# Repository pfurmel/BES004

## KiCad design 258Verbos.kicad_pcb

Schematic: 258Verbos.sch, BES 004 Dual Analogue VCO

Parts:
0.5W1: 2R2; RESISTOR_R0805
10R1: 0.5W; RESISTOR_R0805
C1, C2: 100uF; CP_Radial_D10.0mm_P2.50mm_P5.00mm
C3, C7: .0047uF; CAPACITOR-WIMA_C5B4.5
C4, C8: 15uF; RESISTOR_E2_5-6E
C5, C9: 100pF; C_Rect_L10_W2.5_P5-7.5
C6, C10: 220pf; C_Rect_L10_W2.5_P5-7.5
CONTROL1: ALPHA-9MMA; TOMW_EVUF
D1, D2, D3, D4: 1N4148DO35-7; DIODE_DO35-7
IC1, IC2: CA3140N; SOIC-8-N
J1, J2: J201; SOT-23_Handsoldering
OSC1_CONTROL1, OSC1_FINE1, OSC1_FM_POT1, OSC1_FREQUENCY1, OSC2_FM_POT1: ALPHA-9MMA; TOMW_EVUF
OSC1_FM_IN1, OSC2_FM_IN1: PJ-301B; TOMW_PJ-301B
OSC1_FREQ_TRIM1: 100K; RCL_RTRIM64W
OSC1_SINE_TRIM1, OSC2_SINE_TRIM1: 20k; RCL_RTRIM64W
OSC1_V/OCT_TRIM1: 100R; RCL_RTRIM64W
OSC_1_CONTROL_IN1, OSC_1_V/OCT1, OSC_2CONTROL_IN1, OSC_2_V/OCT1: PJ-301B; TOMW_PJ-301B
OSC_2_FINE1: ALPHA-9MMA; TOMW_EVUF
OSC_2_FREQ_TRIM1: 100K; RCL_RTRIM64W
OSC_2_V/OCT_TRIM1: 100R; RCL_RTRIM64W
OS_2_FREQUENCY1: ALPHA-9MMA; TOMW_EVUF
Q1, Q4: 2N3906; SOT-23_Handsoldering
Q2, Q5: BC847BS; TRANSISTOR-SMALL-SIGNAL_SOT363_PHILIPS
Q3, Q6: J113; SOT-23_Handsoldering
R1, R44: 390K; RESISTOR_R0805
R2, R45: 3K3; RESISTOR_R0805
R3, R7, R20, R24, R46, R50, R63, R67: 10K; RESISTOR_R0805
R4, R47: 3k3; RESISTOR_R0805
R5, R11, R48, R54: 6k8; RESISTOR_R0805
R6, R49: 6K81; RESISTOR_R0805
R8, R51: 33K; RESISTOR_R0805
R9, R52: 68K; RESISTOR_R0805
R10, R53: 1M5; RESISTOR_R0805
R12, R55: 2K49; RESISTOR_R0805
R13, R56: 4K99; RESISTOR_R0805
R14, R18, R19, R57, R61, R62: 15K; RESISTOR_R0805
R15, R58: 20K; RESISTOR_R0805
R16, R27, R59, R70: 330K; RESISTOR_R0805
R17, R22, R26, R32, R60, R65, R69, R75: 680R; RESISTOR_R0805
R21, R25, R30, R35, R64, R68, R73, R78: 100K; RESISTOR_R0805
R23, R66: 330R; RESISTOR_R0805
R28, R71: 15k; RESISTOR_R0805
R29, R72: 68k; RESISTOR_R0805
R31, R74: 1K8; RESISTOR_R0805
R33, R76: 10k; RESISTOR_R0805
R34, R77: 390R; RESISTOR_R0805
R36, R79: 4M7; RESISTOR_R0805
R37, R80: 100k; RESISTOR_R0805
R38, R81: 180K; RESISTOR_R0805
R39, R41, R82, R84: 680k; RESISTOR_R0805
R40, R83: 150k; RESISTOR_R0805
R42, R85: 820k; RESISTOR_R0805
R43, R86: 330k; RESISTOR_R0805
SAW1: 470R; RESISTOR_R0805
SAW2: 150K; RESISTOR_R0805
SAW3: 820K; RESISTOR_R0805
SAW_OUT1: PJ-301B; TOMW_PJ-301B
SAW_WAVESHAPE1: PJ-301B; TOMW_PJ-301B
SAW_WAVESHAPE_Pot1: ALPHA-9MMA; TOMW_EVUF
SAW_WAVESHAPE_TRIM1: 1M; RCL_RTRIM64W
SQ1: 2K2; RESISTOR_R0805
SQ2: 330K; RESISTOR_R0805
SQ3: 680K; RESISTOR_R0805
SQ_OUT1: PJ-301B; TOMW_PJ-301B
SQ_WAVESHAPE1: PJ-301B; TOMW_PJ-301B
SQ_WAVESHAPE_Pot1: ALPHA-9MMA; TOMW_EVUF
SQ_WAVESHAPE_TRIM1: 1M; RCL_RTRIM64W
SV1: TOMW_MA05-2
T1, T2: BC857BS; NXP_60_SOT363
TEMPCO1, TEMPCO2: 2K; RESISTOR_R0805
U1, U4: TL072; SOIC-8-N
U2: LM13700; SO-16-N
U3, U5: TL074; SOIC-14_N

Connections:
+15V: 0.5W1.1, IC1.7 (V+), IC2.7 (V+), OSC1_FINE1.1 (A), OSC1_FREQUENCY1.1 (A), OSC1_FREQ_TRIM1.3 (E), OSC_2_FINE1.1 (A), OSC_2_FREQ_TRIM1.3 (E), OS_2_FREQUENCY1.1 (A), Q1.3 (E), Q2.3 (C), Q4.3 (E), Q5.3 (C), R2.1, R8.1, R45.1, R51.1, SAW_WAVESHAPE_Pot1.1 (A), SQ_WAVESHAPE_Pot1.1 (A), U1.8 (V+), U2.11 (V+), U3.4 (V+), U4.8 (V+), U5.4 (V+)
-15V: 10R1.1, IC1.4 (V-), IC2.4 (V-), OSC1_FREQ_TRIM1.1 (A), OSC_2_FREQ_TRIM1.1 (A), R10.2, R18.2, R19.2, R43.2, R53.2, R61.2, R62.2, R86.2, U1.4 (V-), U2.6 (V-), U3.11 (V-), U4.4 (V-), U5.11 (V-)
/N$1: Q2.1 (E), Q2.4 (E), R19.1, SAW2.2
/N$2: Q1.2 (B), Q2.6 (C), R2.2
/N$3: Q1.1 (C), R6.1, R9.1
/N$4: Q2.2 (B), R6.2, R12.1, R18.1
/N$5: J1.1 (D), R17.1
/N$6: C3.1, U1.2 (-), U2.12 (OUTPUT)
/N$10: R3.2, T1.1 (E), T1.4 (E)
/N$11: C5.2, IC1.6 (OUT), R3.1
/N$12: C5.1, IC1.2 (-IN), R7.2, R10.1, T1.6 (C)
/N$13: IC1.3 (+IN), R1.1
/N$14: C4.+, R7.1
/N$15: OSC1_V/OCT_TRIM1.2 (S), T1.5 (B)
/N$16: OSC1_V/OCT_TRIM1.1 (A), R34.1
/N$17: OSC1_V/OCT_TRIM1.3 (E), TEMPCO1.2, U3.8
/N$18: OSC1_CONTROL1.3 (E), R21.1, R30.2, R35.2, R36.1, R37.2, TEMPCO1.1, U3.9 (-)
/N$19: R21.2, R25.2, U3.1
/N$20: OSC1_CONTROL1.1 (A), R25.1, U3.2 (-)
/N$21: R20.2, U3.3 (+)
/N$22: R31.2, U3.10 (+)
/N$23: C4.-, OSC1_FM_POT1.2 (S)
/N$24: OSC1_FREQUENCY1.2 (S), R30.1
/N$25: T1.3 (C), U2.16 (AMP_BIAS_INPUT)
/N$33: Q3.1 (D), R29.1, SAW3.2, U3.14
/N$34: C6.2, R22.2, R28.1, U3.7
/N$35: Q3.2 (S), R32.1
/N$36: R32.2, SAW1.1, U3.5 (+)
/N$37: Q3.3 (G), SAW_WAVESHAPE_TRIM1.2 (S)
/N$38: R39.2, R41.2, R42.2, R43.1, SAW_WAVESHAPE_TRIM1.1 (A)
/N$39: R39.1, R40.1, SAW_WAVESHAPE1.P$4 (4)
/N$41: R41.1, SAW_WAVESHAPE_Pot1.2 (S)
/N$43: C6.1, OSC1_SINE_TRIM1.1 (A), R4.1, R28.2, U3.6 (-)
/N$44: OSC1_SINE_TRIM1.2 (S), OSC1_SINE_TRIM1.3 (E), R5.1, R11.2
/N$46: D1.A, D2.A, J1.3 (G), R16.1, R27.1
/N$47: C3.2, D1.C, Q2.5 (B), R11.1, R16.2, R17.2, U1.1
/N$49: J1.2 (S), R26.1, SAW1.2
/N$51: 0.5W1.2, C1.+, SV1.9, SV1.10
/N$52: 10R1.2, C2.-, SV1.1, SV1.2
/OSC2: CONTROL1.1 (A), R68.1, U5.2 (-)
GND: C1.-, C2.+, D2.C, D4.C, OSC1_FINE1.3 (E), OSC1_FM_IN1.P$1 (5), OSC1_FM_IN1.P$2 (5), OSC1_FM_POT1.3 (E), OSC1_FREQUENCY1.3 (E), OSC2_FM_IN1.P$1 (5), OSC2_FM_IN1.P$2 (5), OSC2_FM_POT1.3 (E), OSC_1_CONTROL_IN1.P$1 (5), OSC_1_CONTROL_IN1.P$2 (5), OSC_1_V/OCT1.P$1 (5), OSC_1_V/OCT1.P$2 (5), OSC_2CONTROL_IN1.P$1 (5), OSC_2CONTROL_IN1.P$2 (5), OSC_2_FINE1.3 (E), OSC_2_V/OCT1.P$1 (5), OSC_2_V/OCT1.P$2 (5), OS_2_FREQUENCY1.3 (E), R1.2, R4.2, R5.2, R12.2, R13.2, R14.2, R20.1, R24.2, R26.2, R27.2, R31.1, R33.1, R34.2, R40.2, R42.1, R44.2, R47.2, R48.2, R55.2, R56.2, R57.2, R63.1, R67.2, R69.2, R70.2, R74.1, R76.1, R77.2, R83.2, R85.1, SAW_OUT1.P$1 (5), SAW_OUT1.P$2 (5), SAW_WAVESHAPE1.P$1 (5), SAW_WAVESHAPE1.P$2 (5), SAW_WAVESHAPE_Pot1.3 (E), SQ3.1, SQ_OUT1.P$1 (5), SQ_OUT1.P$2 (5), SQ_WAVESHAPE1.P$1 (5), SQ_WAVESHAPE1.P$2 (5), SQ_WAVESHAPE_Pot1.3 (E), SV1.3, SV1.4, SV1.5, SV1.6, SV1.7, SV1.8, T1.2 (B), T2.2 (B), U1.3 (+), U4.3 (+)
unnamed: C7.1, U2.5 (OUTPUT), U4.2 (-)
unnamed: C7.2, D3.C, Q5.5 (B), R54.1, R59.2, R60.2, U4.1
unnamed: C8.+, R50.1
unnamed: C8.-, OSC2_FM_POT1.2 (S)
unnamed: C9.1, IC2.2 (-IN), R50.2, R53.1, T2.6 (C)
unnamed: C9.2, IC2.6 (OUT), R46.1
unnamed: C10.1, OSC2_SINE_TRIM1.1 (A), R47.1, R71.2, U5.13 (-)
unnamed: C10.2, R65.2, R71.1, U5.14
unnamed: CONTROL1.2 (S), R81.2
unnamed: CONTROL1.3 (E), R64.1, R73.2, R78.2, R79.1, R80.2, TEMPCO2.1, U5.6 (-)
unnamed: D3.A, D4.A, J2.3 (G), R59.1, R70.1
unnamed: IC2.3 (+IN), R44.1
unnamed: J2.1 (D), R60.1
unnamed: J2.2 (S), R69.1, SQ1.2
unnamed: OSC1_CONTROL1.2 (S), R38.2
unnamed: OSC1_FINE1.2 (S), R36.2
unnamed: OSC1_FM_IN1.P$4 (4), OSC1_FM_POT1.1 (A)
unnamed: OSC1_FREQ_TRIM1.2 (S), R35.1
unnamed: OSC2_FM_IN1.P$4 (4), OSC2_FM_POT1.1 (A)
unnamed: OSC2_SINE_TRIM1.2 (S), OSC2_SINE_TRIM1.3 (E), R48.1, R54.2
unnamed: OSC_1_CONTROL_IN1.P$4 (4), R38.1
unnamed: OSC_1_V/OCT1.P$4 (4), R37.1
unnamed: OSC_2CONTROL_IN1.P$4 (4), R81.1
unnamed: OSC_2_FINE1.2 (S), R79.2
unnamed: OSC_2_FREQ_TRIM1.2 (S), R78.1
unnamed: OSC_2_V/OCT1.P$4 (4), R80.1
unnamed: OSC_2_V/OCT_TRIM1.1 (A), R77.1
unnamed: OSC_2_V/OCT_TRIM1.2 (S), T2.5 (B)
unnamed: OSC_2_V/OCT_TRIM1.3 (E), TEMPCO2.2, U5.7
unnamed: OS_2_FREQUENCY1.2 (S), R73.1
unnamed: Q4.1 (C), R49.1, R52.1
unnamed: Q4.2 (B), Q5.6 (C), R45.2
unnamed: Q5.1 (E), Q5.4 (E), R62.1
unnamed: Q5.2 (B), R49.2, R55.1, R61.1, SQ2.2
unnamed: Q6.1 (D), R72.1, U5.8
unnamed: Q6.2 (S), R75.1
unnamed: Q6.3 (G), SQ_WAVESHAPE_TRIM1.2 (S)
unnamed: R8.2, R13.1, U2.14 (INPUT(+))
unnamed: R9.2, R14.1, U2.13 (INPUT(-))
unnamed: R15.1, R23.2, U1.7
unnamed: R15.2, R24.1, U1.6 (-)
unnamed: R22.1, U1.5 (+)
unnamed: R23.1, SAW_OUT1.P$4 (4)
unnamed: R29.2, SAW2.1, U3.13 (-)
unnamed: R33.2, U3.12 (+)
unnamed: R46.2, T2.1 (E), T2.4 (E)
unnamed: R51.2, R56.1, U2.3 (INPUT(+))
unnamed: R52.2, R57.1, U2.4 (INPUT(-))
unnamed: R58.1, R66.2, U4.7
unnamed: R58.2, R67.1, U4.6 (-)
unnamed: R63.2, U5.3 (+)
unnamed: R64.2, R68.2, U5.1
unnamed: R65.1, U4.5 (+)
unnamed: R66.1, SQ_OUT1.P$4 (4)
unnamed: R72.2, SQ2.1, U5.9 (-)
unnamed: R74.2, U5.5 (+)
unnamed: R75.2, SQ1.1, U5.12 (+)
unnamed: R76.2, U5.10 (+)
unnamed: R82.1, R83.1, SQ_WAVESHAPE1.P$4 (4)
unnamed: R82.2, R84.2, R85.2, R86.1, SQ_WAVESHAPE_TRIM1.1 (A)
unnamed: R84.1, SQ_WAVESHAPE_Pot1.2 (S)
unnamed: SAW3.1, SAW_WAVESHAPE_TRIM1.3 (E)
unnamed: SQ3.2, SQ_WAVESHAPE_TRIM1.3 (E)
unnamed: T2.3 (C), U2.1 (AMP_BIAS_INPUT)

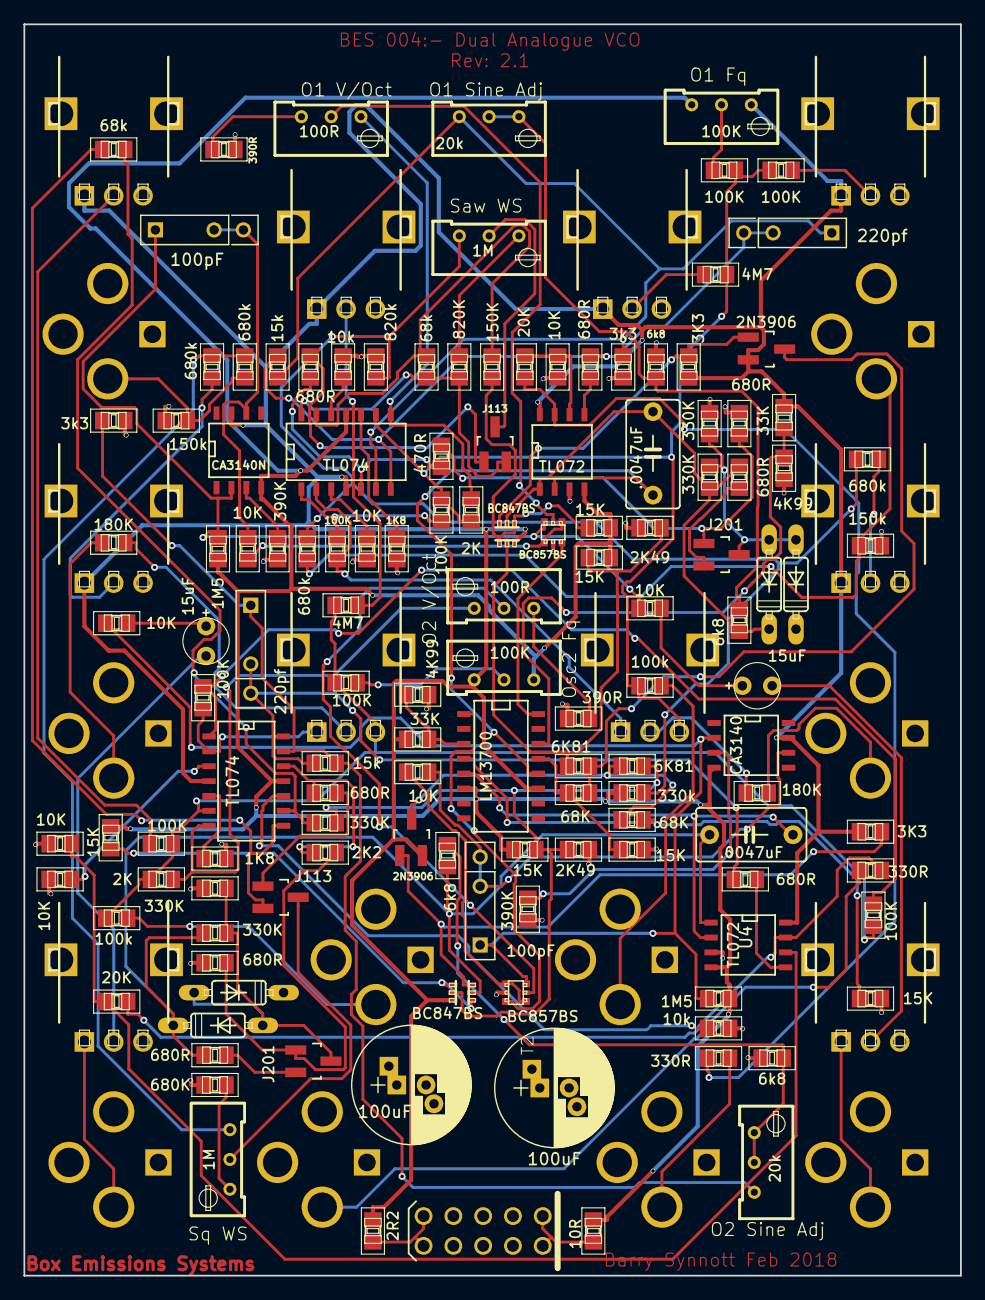
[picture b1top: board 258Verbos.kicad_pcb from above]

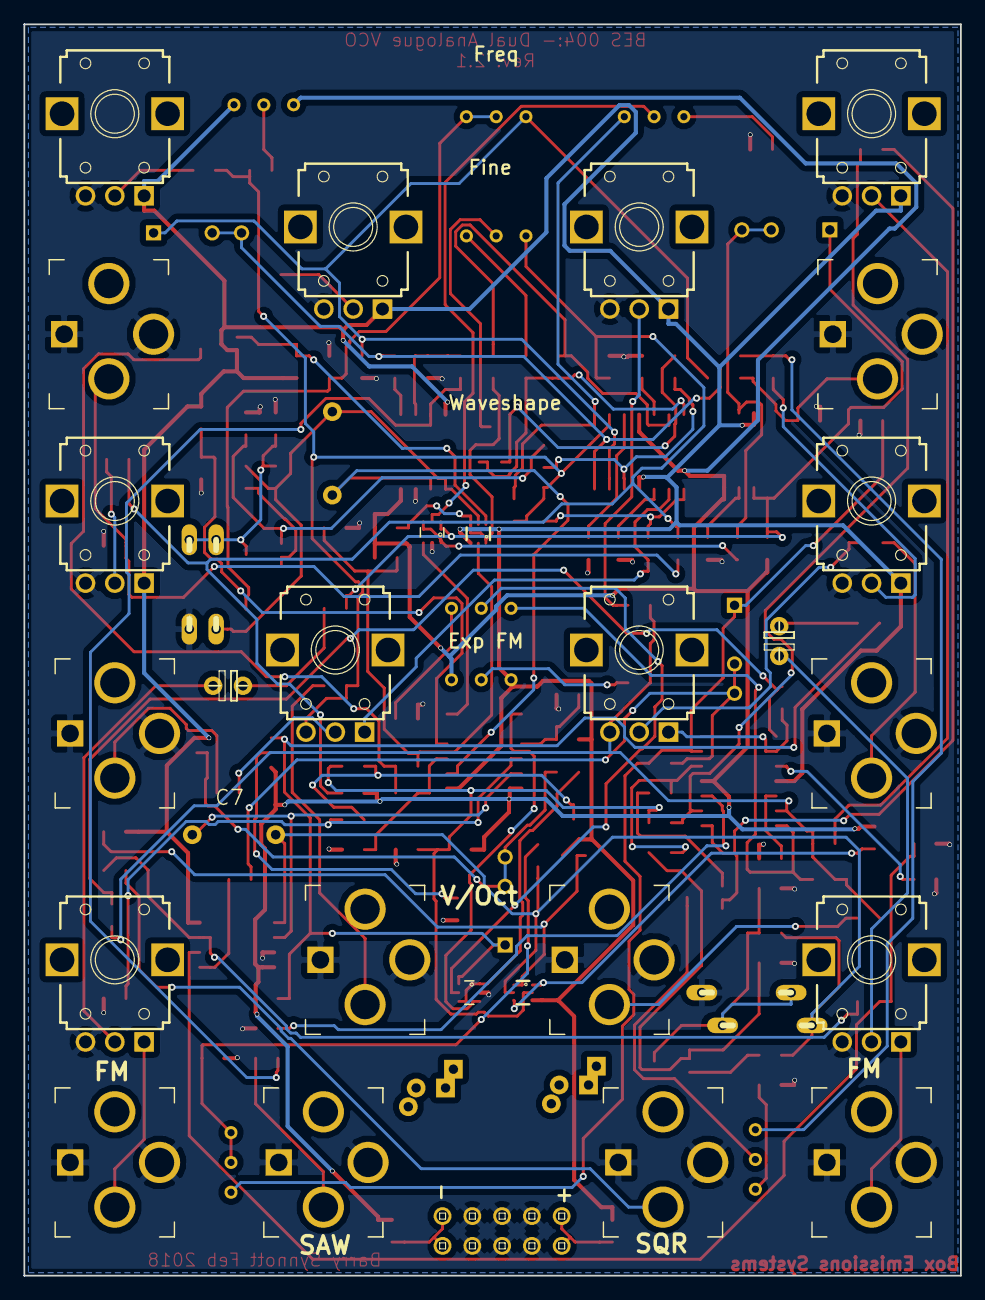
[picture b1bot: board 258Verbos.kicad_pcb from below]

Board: 2 copper layers, 79.9 x 106.7 mm, 154 parts (17 on the bottom side), 105 nets.

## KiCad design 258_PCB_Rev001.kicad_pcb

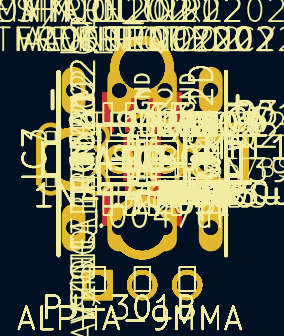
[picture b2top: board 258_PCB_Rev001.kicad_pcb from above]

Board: 2 copper layers, 82 parts (0 on the bottom side), 52 nets, no tracks yet.

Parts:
0.5W202: 33K; RESISTOR_R0805
10R202: 0.5W; RESISTOR_R0805
C2: .0047uF; CAPACITOR-WIMA_C5B4.5
C3: 100pF; CAPACITOR-WIMA_C2.5-3
C4: 15uF; RESISTOR_E2_5-6E
C5: 220pf; CAPACITOR-WIMA_C2.5-3
C6, C7: 100uF; RESISTOR_E2_5-6E
CONTROL202: ALPHA-9MMA; TOMW_EVUF
CONTROL_IN202: PJ-301B; TOMW_PJ-301B
D1, D2: 1N4148DO35-7; DIODE_DO35-7
FINE202: ALPHA-9MMA; TOMW_EVUF
FM_IN202: PJ-301B; TOMW_PJ-301B
FM_POT202: ALPHA-9MMA; TOMW_EVUF
FREQUENCY202: ALPHA-9MMA; TOMW_EVUF
FREQ_TRIM202: 100K; RCL_RTRIM64W
IC2: TL071D; LINEAR_SO08
IC3: CA3140N; LINEAR_DIL08
IC4, IC5B1, IC6A1: TL072D; LINEAR_SO08
IC7: CA3080E; OTA_DIL08
INITIAL_FREQUENCY202: ALPHA-9MMA; TOMW_EVUF
J201: MPF102; BT_TRANSISTOR_TO92F
MAIN_OUT202: PJ-301B; TOMW_PJ-301B
Q1: BC847BS; TRANSISTOR-SMALL-SIGNAL_SOT363_PHILIPS
Q2: 2N3906; TRANSISTOR-PNP_TO92
Q3: MPF102; BT_TRANSISTOR_TO92F
R1, R3, R9: 15K; RESISTOR_R0805
R2: 6K81; RESISTOR_R0805
R4: 2K49; RESISTOR_R0805
R5: 4K99; RESISTOR_R0805
R6: 3K3; RESISTOR_R0805
R7: 33K; RESISTOR_R0805
R8: 68K; RESISTOR_R0805
R10, R12, R19: 10K; RESISTOR_R0805
R11: 390K; RESISTOR_R0805
R13: 1M5; RESISTOR_R0805
R14: 10k; RESISTOR_R0805
R15: 390R; RESISTOR_R0805
R16, R17, R18, R21: 100K; RESISTOR_R0805
R20: 1K8; RESISTOR_R0805
R22: 180K; RESISTOR_R0805
R23: 100k; RESISTOR_R0805
R24: 68k; RESISTOR_R0805
R25, R31, R36, R37: 680R; RESISTOR_R0805
R26: 330k; RESISTOR_R0805
R27, R29: 680k; RESISTOR_R0805
R28: 150k; RESISTOR_R0805
R30: 820k; RESISTOR_R0805
R32: 15k; RESISTOR_R0805
R33, R34: 6k8; RESISTOR_R0805
R35: 3k3; RESISTOR_R0805
R38, R39: 330K; RESISTOR_R0805
SIN/SQ1, SIN/SQ2, SIN/SQ3, SIN/SQ4, SIN/SQ5: 0; RESISTOR_R0805
SINE_TRIM202: 20k; RCL_RTRIM64W
SV1: TOMW_MA05-2
T1: BC857BS; NXP_60_SOT363
TEMPCO202: 2K; RESISTOR_R0805
V/OCT202: PJ-301B; TOMW_PJ-301B
V/OCT_TRIM202: 100R; RCL_RTRIM64W
WAVESHAPE202: ALPHA-9MMA; TOMW_EVUF
WAVESHAPE_CTRL202: PJ-301B; TOMW_PJ-301B
WAVESHAPE_TRIM202: 1M; RCL_RTRIM64W

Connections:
+15V: 0.5W202.1, FREQUENCY202.3, FREQ_TRIM202.3, IC2.7, IC3.7, INITIAL_FREQUENCY202.3, Q1.3, Q2.3, R6.1, R7.2, SV1.9, WAVESHAPE202.3
-15V: 10R202.1, FREQ_TRIM202.1, IC2.4, IC3.4, INITIAL_FREQUENCY202.1, R1.2, R3.2, R13.2, R26.2, SV1.1
/N$1: Q1.1, Q1.4, R1.1, SIN/SQ1.2
/N$2: Q1.6, Q2.2, R6.2
/N$3: Q2.1, R2.1, R8.2
/N$4: Q1.2, R2.2, R3.1, R4.1, SIN/SQ2.2
/N$5: J201.1, R36.1
/N$6: C2.1, IC2.2, IC7.6
/N$7: IC7.3, R5.1, R7.1
/N$9: IC7.2, R8.1, R9.1
/N$10: R10.2, T1.1, T1.4
/N$11: C3.2, IC3.6, R10.1
/N$12: C3.1, IC3.2, R12.2, R13.1, T1.6
/N$13: IC3.3, R11.1
/N$14: C4.+, R12.1
/N$15: T1.5, V/OCT_TRIM202.2
/N$16: R15.1, V/OCT_TRIM202.1
/N$17: IC4.7, TEMPCO202.2, V/OCT_TRIM202.3
/N$18: CONTROL202.1, FREQ_TRIM202.2, IC4.6, R16.2, R17.1, R21.2, R23.2, TEMPCO202.1
/N$19: IC4.1, R17.2, R18.2
/N$20: CONTROL202.3, IC4.2, R18.1
/N$21: IC4.3, R19.2
/N$22: IC4.5, R20.2
/N$23: C4.-, FM_POT202.2
/N$24: FREQUENCY202.2, R16.1
/N$25: IC7.5, T1.3
/N$26: INITIAL_FREQUENCY202.2, R21.1
/N$27: FM_IN202.P$3, FM_POT202.3
/N$28: CONTROL_IN202.P$3, R22.1
/N$29: CONTROL202.2, R22.2
/N$30: R23.1, V/OCT202.P$3
/N$31: IC5B1.5, R14.2
/N$32: IC5B1.6, R24.1, SIN/SQ1.1, SIN/SQ2.1
/N$33: IC5B1.7, Q3.1, R24.2, SIN/SQ4.1
/N$34: C5.2, IC6A1.1, R31.2, R32.1
/N$35: Q3.2, R25.1
/N$36: IC6A1.3, R25.2, SIN/SQ5.1
/N$37: Q3.3, WAVESHAPE_TRIM202.2
/N$38: SIN/SQ3.1, SIN/SQ4.2, WAVESHAPE_TRIM202.1
/N$39: R27.1, R28.1, WAVESHAPE_CTRL202.P$3
/N$40: R26.1, R27.2, R29.2, R30.2, WAVESHAPE_TRIM202.3
/N$41: R29.1, WAVESHAPE202.2
/N$42: MAIN_OUT202.P$3, R31.1
/N$43: C5.1, IC6A1.2, R32.2, R35.1, SINE_TRIM202.1
/N$44: R33.2, R34.1, SINE_TRIM202.2, SINE_TRIM202.3
/N$46: D1.A, D2.A, J201.3, R38.1, R39.1
/N$47: C2.2, D1.C, IC2.6, Q1.5, R33.1, R36.2, R38.2
/N$49: J201.2, R37.1, SIN/SQ5.2
/N$51: 0.5W202.2, C6.+, SV1.10
/N$52: 10R202.2, C7.-, SV1.2
/N$54: FINE202.3, FREQUENCY202.1
GND: C6.-, C7.+, CONTROL_IN202.P$1, CONTROL_IN202.P$2, D2.C, FINE202.1, FINE202.2, FM_IN202.P$1, FM_IN202.P$2, FM_POT202.1, IC2.3, MAIN_OUT202.P$1, MAIN_OUT202.P$2, R4.2, R5.2, R9.2, R11.2, R14.1, R15.2, R19.1, R20.1, R28.2, R30.1, R34.2, R35.2, R37.2, R39.2, SIN/SQ3.2, SV1.3, SV1.4, SV1.5, SV1.6, SV1.7, SV1.8, T1.2, V/OCT202.P$1, V/OCT202.P$2, WAVESHAPE202.1, WAVESHAPE_CTRL202.P$1, WAVESHAPE_CTRL202.P$2

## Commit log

2018-02-06 Modified footprint for pots. Changed silkscreen text. Rerouted
